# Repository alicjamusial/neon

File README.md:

# NEON - FT4232H Mini Module Adapter 

### about the project

 Neon is a PCB project designed as an adapter for FTDI FT4232H Mini Module board. It includes four two rows UART sockets (A, B, C, D) for easy plugging in logic analyzer and LEDs on both TX/RX and USB power supply. Its main goal is to improve the experience of using FTDI Mini Module and allow to quickly and easily debug any possible issues. It was designed using [KiCad](https://kicad.org/).

Version 1.0 is available [in the releases section](https://github.com/alicjamusial/neon/releases/tag/neon-v.1.0).

### usage
To be able to use Neon powered by USB two jumpers needs to be placed on the board (on J1 (3V3 & VIO) and J5 (VCC & VBUS) elements).

### license
Neon is available on Creative Commons Attribution Share Alike 4.0 International license (more in [license file](LICENSE.txt)). You are free to use it, modify it and produce as many of your own neons as you need :)

### assembled neon ✨

#### TODO in version 1.1
* label for D9 LED on board,
* labels for the directions of all LEDs on board,
* ...any ideas/fixes/improvements/PRs are welcomed :)

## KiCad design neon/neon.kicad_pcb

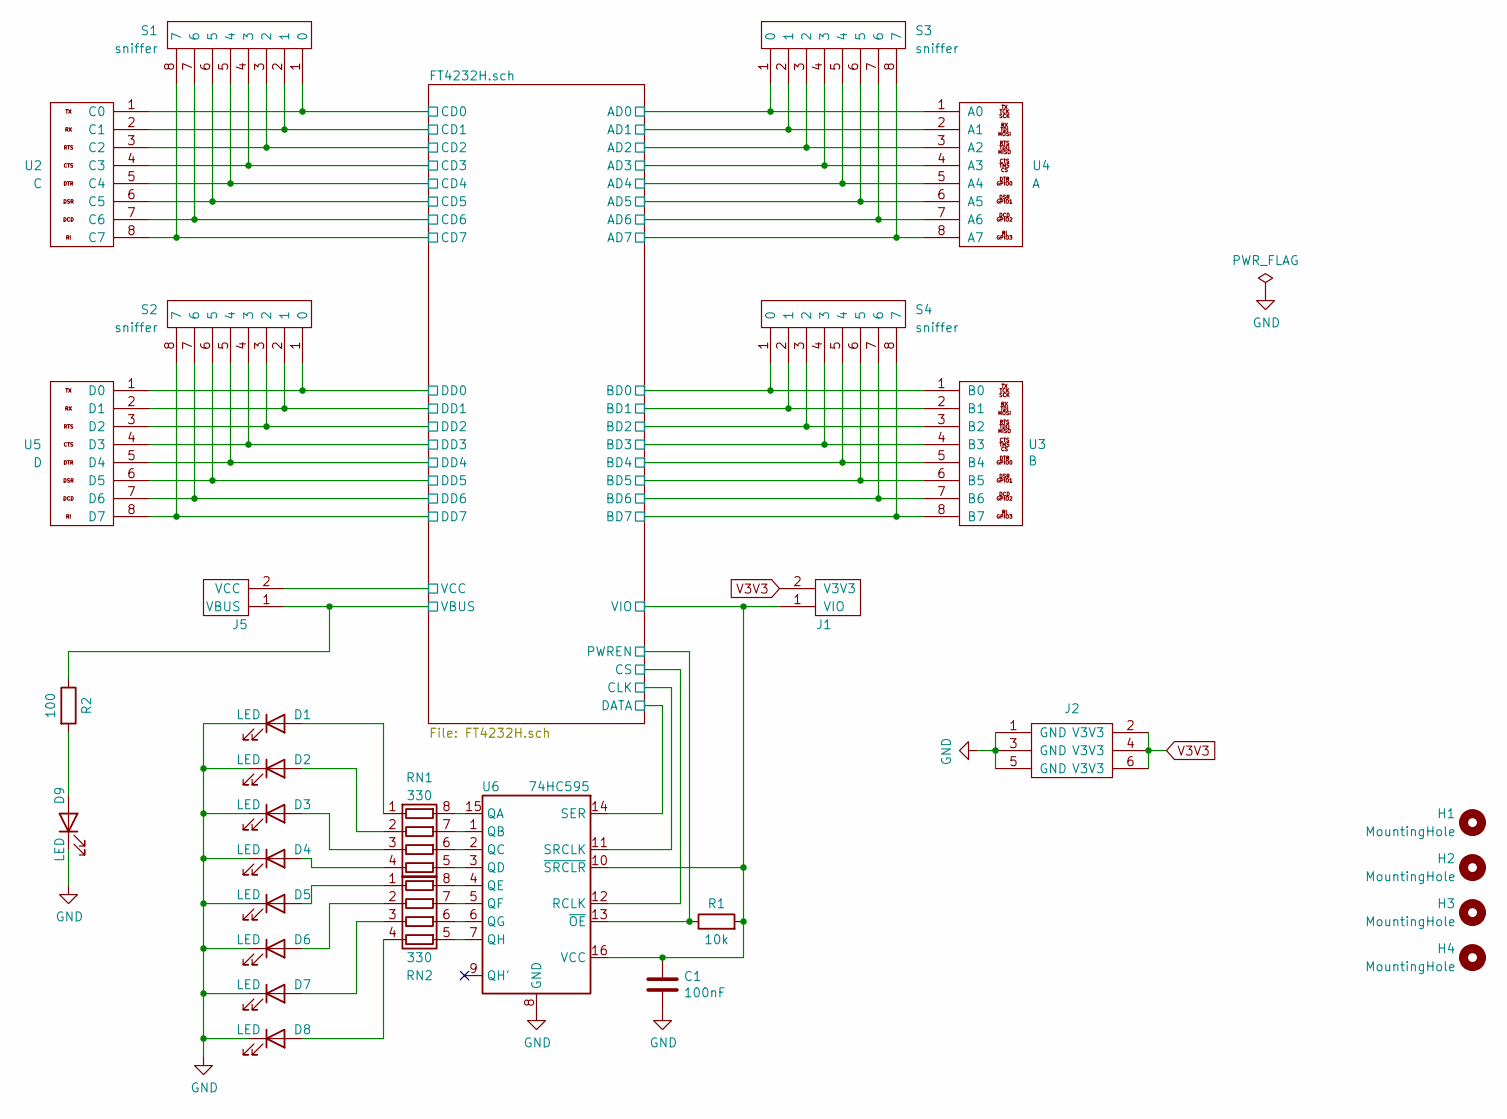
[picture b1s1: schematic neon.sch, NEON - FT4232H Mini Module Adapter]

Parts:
C1: 100nF; C_0805_2012Metric
D1, D2, D3, D4, D5, D6, D7, D8, D9: LED; LED_0805_2012Metric
H1, H2, H3, H4: MountingHole; MountingHole_3.2mm_M3
J1: V3V3-VIO; PinHeader_1x02_P2.54mm_Vertical
J2: 3xV3V3-GND; PinHeader_2x03_P2.54mm_Vertical
J5: VBUS-VCC; PinHeader_1x02_P2.54mm_Vertical
R1: 10k; R_0805_2012Metric
R2: 100; R_0805_2012Metric
RN1, RN2: 330; R_Array_Convex_4x0603
S1, S2, S3, S4: sniffer; PinHeader_1x08_P2.54mm_Vertical
U2: C; PinHeader_1x08_P2.54mm_Vertical
U3: B; PinHeader_1x08_P2.54mm_Vertical
U4: A; PinHeader_1x08_P2.54mm_Vertical
U5: D; PinHeader_1x08_P2.54mm_Vertical
U6: 74HC595; SOIC-16_3.9x9.9mm_P1.27mm

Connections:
/FT4232H.sch/AD0: S3.1 (0), U4.1 (A0); also elsewhere on the board
/FT4232H.sch/AD1: S3.2 (1), U4.2 (A1); also elsewhere on the board
/FT4232H.sch/AD2: S3.3 (2), U4.3 (A2); also elsewhere on the board
/FT4232H.sch/AD3: S3.4 (3), U4.4 (A3); also elsewhere on the board
/FT4232H.sch/AD4: S3.5 (4), U4.5 (A4); also elsewhere on the board
/FT4232H.sch/AD5: S3.6 (5), U4.6 (A5); also elsewhere on the board
/FT4232H.sch/AD6: S3.7 (6), U4.7 (A6); also elsewhere on the board
/FT4232H.sch/AD7: S3.8 (7), U4.8 (A7); also elsewhere on the board
/FT4232H.sch/BD0: S4.1 (0), U3.1 (B0); also elsewhere on the board
/FT4232H.sch/BD1: S4.2 (1), U3.2 (B1); also elsewhere on the board
/FT4232H.sch/BD2: S4.3 (2), U3.3 (B2); also elsewhere on the board
/FT4232H.sch/BD3: S4.4 (3), U3.4 (B3); also elsewhere on the board
/FT4232H.sch/BD4: S4.5 (4), U3.5 (B4); also elsewhere on the board
/FT4232H.sch/BD5: S4.6 (5), U3.6 (B5); also elsewhere on the board
/FT4232H.sch/BD6: S4.7 (6), U3.7 (B6); also elsewhere on the board
/FT4232H.sch/BD7: S4.8 (7), U3.8 (B7); also elsewhere on the board
/FT4232H.sch/CD0: S1.1 (0), U2.1 (C0); also elsewhere on the board
/FT4232H.sch/CD1: S1.2 (1), U2.2 (C1); also elsewhere on the board
/FT4232H.sch/CD2: S1.3 (2), U2.3 (C2); also elsewhere on the board
/FT4232H.sch/CD3: S1.4 (3), U2.4 (C3); also elsewhere on the board
/FT4232H.sch/CD4: S1.5 (4), U2.5 (C4); also elsewhere on the board
/FT4232H.sch/CD5: S1.6 (5), U2.6 (C5); also elsewhere on the board
/FT4232H.sch/CD6: S1.7 (6), U2.7 (C6); also elsewhere on the board
/FT4232H.sch/CD7: S1.8 (7), U2.8 (C7); also elsewhere on the board
/FT4232H.sch/CLK: U6.11 (SRCLK); also elsewhere on the board
/FT4232H.sch/CS: U6.12 (RCLK); also elsewhere on the board
/FT4232H.sch/DATA: U6.14 (SER); also elsewhere on the board
/FT4232H.sch/DD0: S2.1 (0), U5.1 (D0); also elsewhere on the board
/FT4232H.sch/DD1: S2.2 (1), U5.2 (D1); also elsewhere on the board
/FT4232H.sch/DD2: S2.3 (2), U5.3 (D2); also elsewhere on the board
/FT4232H.sch/DD3: S2.4 (3), U5.4 (D3); also elsewhere on the board
/FT4232H.sch/DD4: S2.5 (4), U5.5 (D4); also elsewhere on the board
/FT4232H.sch/DD5: S2.6 (5), U5.6 (D5); also elsewhere on the board
/FT4232H.sch/DD6: S2.7 (6), U5.7 (D6); also elsewhere on the board
/FT4232H.sch/DD7: S2.8 (7), U5.8 (D7); also elsewhere on the board
/FT4232H.sch/PWREN: R1.1, U6.13 (~OE); also elsewhere on the board
/FT4232H.sch/VBUS: J5.1 (VBUS), R2.1; also elsewhere on the board
/FT4232H.sch/VCC: J5.2 (VCC); also elsewhere on the board
/FT4232H.sch/VIO: C1.1, J1.1 (VIO), R1.2, U6.10 (~SRCLR), U6.16 (VCC); also elsewhere on the board
GND: C1.2, D1.1 (K), D2.1 (K), D3.1 (K), D4.1 (K), D5.1 (K), D6.1 (K), D7.1 (K), D8.1 (K), D9.1 (K), J2.1 (GND), J2.3 (GND), J2.5 (GND), U6.8 (GND); also elsewhere on the board
unnamed: D1.2 (A), RN1.1 (R1.1)
unnamed: D2.2 (A), RN1.2 (R2.1)
unnamed: D3.2 (A), RN1.3 (R3.1)
unnamed: D4.2 (A), RN1.4 (R4.1)
unnamed: D5.2 (A), RN2.1 (R1.1)
unnamed: D6.2 (A), RN2.2 (R2.1)
unnamed: D7.2 (A), RN2.3 (R3.1)
unnamed: D8.2 (A), RN2.4 (R4.1)
unnamed: D9.2 (A), R2.2
unnamed: RN1.5 (R4.2), U6.3 (QD)
unnamed: RN1.6 (R3.2), U6.2 (QC)
unnamed: RN1.7 (R2.2), U6.1 (QB)
unnamed: RN1.8 (R1.2), U6.15 (QA)
unnamed: RN2.5 (R4.2), U6.7 (QH)
unnamed: RN2.6 (R3.2), U6.6 (QG)
unnamed: RN2.7 (R2.2), U6.5 (QF)
unnamed: RN2.8 (R1.2), U6.4 (QE)
V3V3: J1.2 (V3V3), J2.2 (V3V3), J2.4 (V3V3), J2.6 (V3V3); also elsewhere on the board

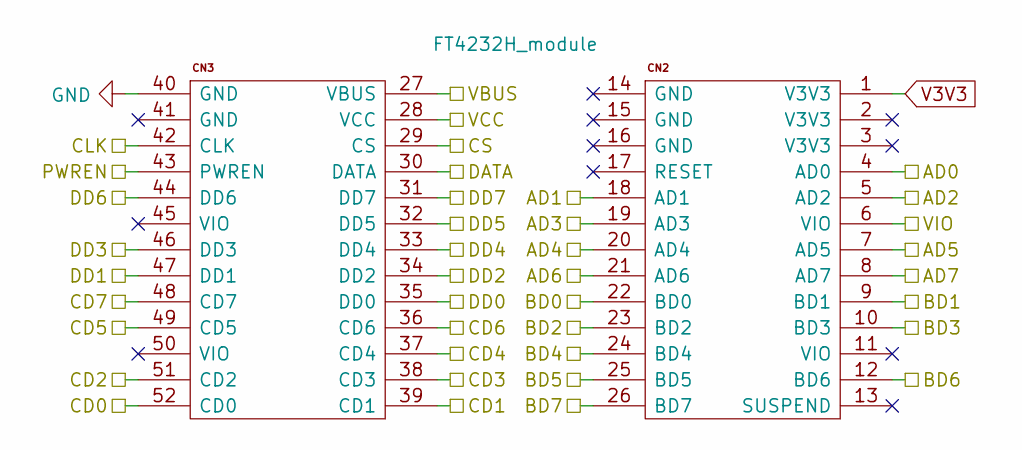
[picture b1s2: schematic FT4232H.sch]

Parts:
U1: FT4232H_module; FT4232H-MINI-MODULE-2

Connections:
/FT4232H.sch/AD0: U1.4 (AD0); also elsewhere on the board
/FT4232H.sch/AD1: U1.18 (AD1); also elsewhere on the board
/FT4232H.sch/AD2: U1.5 (AD2); also elsewhere on the board
/FT4232H.sch/AD3: U1.19 (AD3); also elsewhere on the board
/FT4232H.sch/AD4: U1.20 (AD4); also elsewhere on the board
/FT4232H.sch/AD5: U1.7 (AD5); also elsewhere on the board
/FT4232H.sch/AD6: U1.21 (AD6); also elsewhere on the board
/FT4232H.sch/AD7: U1.8 (AD7); also elsewhere on the board
/FT4232H.sch/BD0: U1.22 (BD0); also elsewhere on the board
/FT4232H.sch/BD1: U1.9 (BD1); also elsewhere on the board
/FT4232H.sch/BD2: U1.23 (BD2); also elsewhere on the board
/FT4232H.sch/BD3: U1.10 (BD3); also elsewhere on the board
/FT4232H.sch/BD4: U1.24 (BD4); also elsewhere on the board
/FT4232H.sch/BD5: U1.25 (BD5); also elsewhere on the board
/FT4232H.sch/BD6: U1.12 (BD6); also elsewhere on the board
/FT4232H.sch/BD7: U1.26 (BD7); also elsewhere on the board
/FT4232H.sch/CD0: U1.52 (CD0); also elsewhere on the board
/FT4232H.sch/CD1: U1.39 (CD1); also elsewhere on the board
/FT4232H.sch/CD2: U1.51 (CD2); also elsewhere on the board
/FT4232H.sch/CD3: U1.38 (CD3); also elsewhere on the board
/FT4232H.sch/CD4: U1.37 (CD4); also elsewhere on the board
/FT4232H.sch/CD5: U1.49 (CD5); also elsewhere on the board
/FT4232H.sch/CD6: U1.36 (CD6); also elsewhere on the board
/FT4232H.sch/CD7: U1.48 (CD7); also elsewhere on the board
/FT4232H.sch/CLK: U1.42 (CLK); also elsewhere on the board
/FT4232H.sch/CS: U1.29 (CS); also elsewhere on the board
/FT4232H.sch/DATA: U1.30 (DATA); also elsewhere on the board
/FT4232H.sch/DD0: U1.35 (DD0); also elsewhere on the board
/FT4232H.sch/DD1: U1.47 (DD1); also elsewhere on the board
/FT4232H.sch/DD2: U1.34 (DD2); also elsewhere on the board
/FT4232H.sch/DD3: U1.46 (DD3); also elsewhere on the board
/FT4232H.sch/DD4: U1.33 (DD4); also elsewhere on the board
/FT4232H.sch/DD5: U1.32 (DD5); also elsewhere on the board
/FT4232H.sch/DD6: U1.44 (DD6); also elsewhere on the board
/FT4232H.sch/DD7: U1.31 (DD7); also elsewhere on the board
/FT4232H.sch/PWREN: U1.43 (PWREN); also elsewhere on the board
/FT4232H.sch/VBUS: U1.27 (VBUS); also elsewhere on the board
/FT4232H.sch/VCC: U1.28 (VCC); also elsewhere on the board
/FT4232H.sch/VIO: U1.6 (VIO); also elsewhere on the board
GND: U1.40 (GND); also elsewhere on the board
V3V3: U1.1 (V3V3); also elsewhere on the board

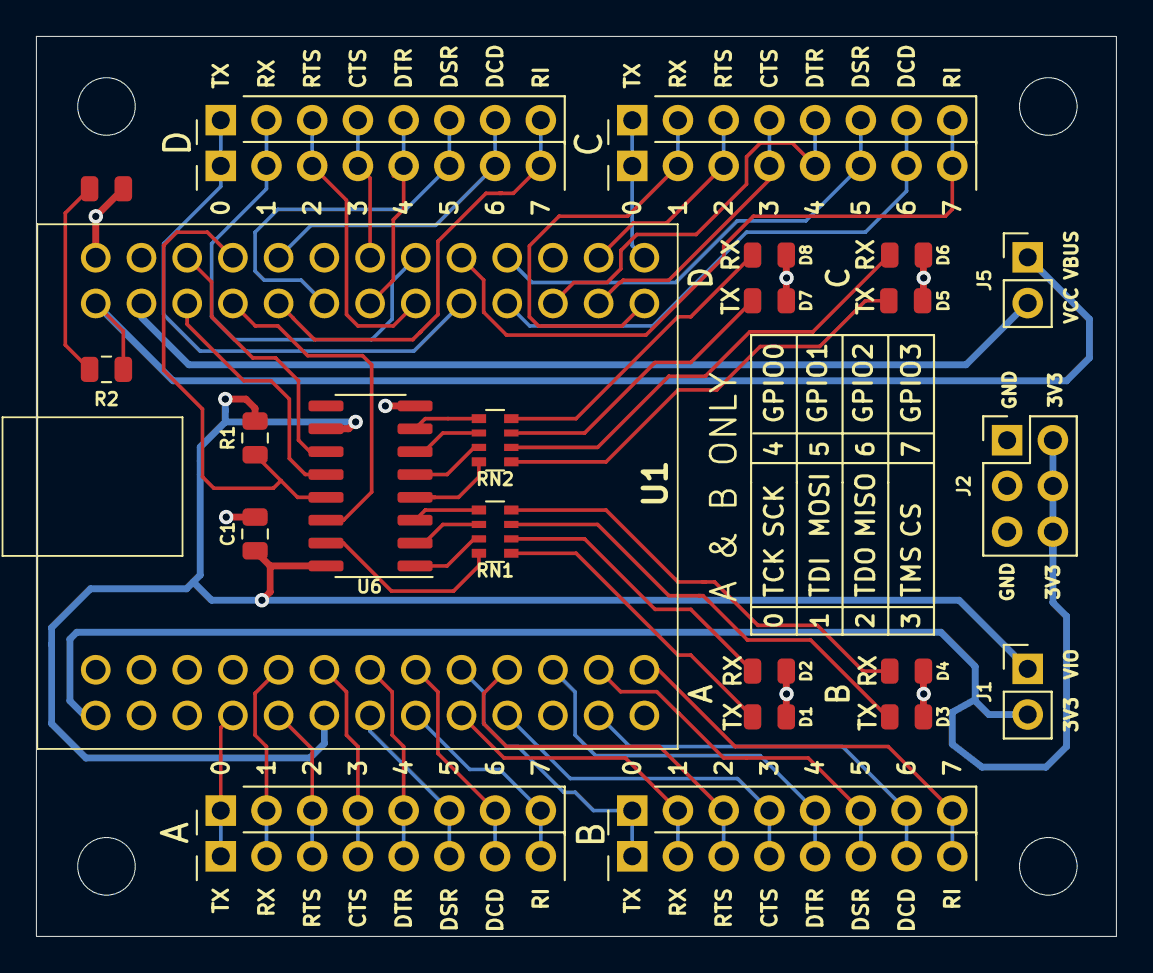
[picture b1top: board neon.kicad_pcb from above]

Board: 2 copper layers, 60.0 x 50.0 mm, 31 parts (0 on the bottom side), 58 nets.

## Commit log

2020-08-29 Repo init
2020-08-29 Add FT4232H module pinouts
2020-08-29 Add gitignore
2020-08-29 Hierarchical version - draft
2020-08-29 Add all hierarchical pins
2020-08-29 Add more hierarchical pins
2020-08-29 B, C & D buses
2020-08-30 V3V3 & GND pings
2020-08-30 Add LEDs
2020-08-30 Annotate components
2020-08-30 Assign footprints - part 1 and buggy
2020-08-30 Change pins numbers on FTDI symbol
2020-08-30 Pin warning fixes
2020-08-30 Start numbering pins from 1
2020-08-30 Order pins on footprint - part 1
2020-08-30 Order pins on footprint - part 2
2020-08-30 Board cuts - part 1
2020-08-30 FTDI centered (almost)
2020-08-30 Restore lost pin
2020-08-30 Labels adjustments
2020-08-30 Remove bak
2020-08-30 With transistors
2020-08-30 Version with shift register - schematic
2020-08-30 Assign LEDs on pcb
2020-08-30 A BUS
2020-08-31 Texts ideas
2020-08-31 More labels
2020-08-31 Labels four versions
2020-08-31 With table and LEDs underneath the ftdi
2020-09-01 Add sniffer
2020-09-01 Sniffer PCB - draft
2020-09-01 All sniffers on PCB
2020-09-01 Fixes
2020-09-01 Problems fixes
2020-09-01 Center things & rotate J1 & J5
2020-09-01 A, B, C & D distances
2020-09-02 Add 3x2 connector for GND&3v3
2020-09-02 Add LED to VBUS
2020-09-02 Bigger letters & remove random dot
2020-09-02 Small fixes
2020-09-02 Move LED, fix H4&H2 and some paths
2020-09-02 Move register & some paths
2020-09-02 Buses paths
2020-09-02 A & B buses
2020-09-02 LEDs paths
2020-09-02 C paths
2020-09-02 Fix for Maciek's OCD
2020-09-02 D bus
2020-09-03 Fix nets width
2020-09-03 Draw all nets
2020-09-03 Fill GND plane
2020-09-03 Add logo
2020-09-03 Fix nets too close to pads
2020-09-03 Small logo update
2020-10-01 Add readme & photos
2021-11-09 Update README.md
    https://forum.kicad.info/t/warning-avoid-all-links-to-kicad-pcb-org-use-kicad-org/31521
